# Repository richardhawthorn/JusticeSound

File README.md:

### Description

Justice Cross

### Features

- 28 LED display
- Charlieplex LED control
- ATTINY44 processor
- 3V operation @ 1Mhz or 8Mhz
- 1x button
- ICSP port
- Hole for necklace chain

### License

This work is licensed under a Creative Commons Attribution-ShareAlike 4.0 International License.

<br />
Designed by <a xmlns:cc="http://creativecommons.org/ns#" href="http://www.richardhawthorn.com" property="cc:attributionName" rel="cc:attributionURL" target="_blank">Richard Hawthorn</a><br />
<a rel="license" href="http://creativecommons.org/licenses/by-sa/4.0/" target="_blank">View License</a>

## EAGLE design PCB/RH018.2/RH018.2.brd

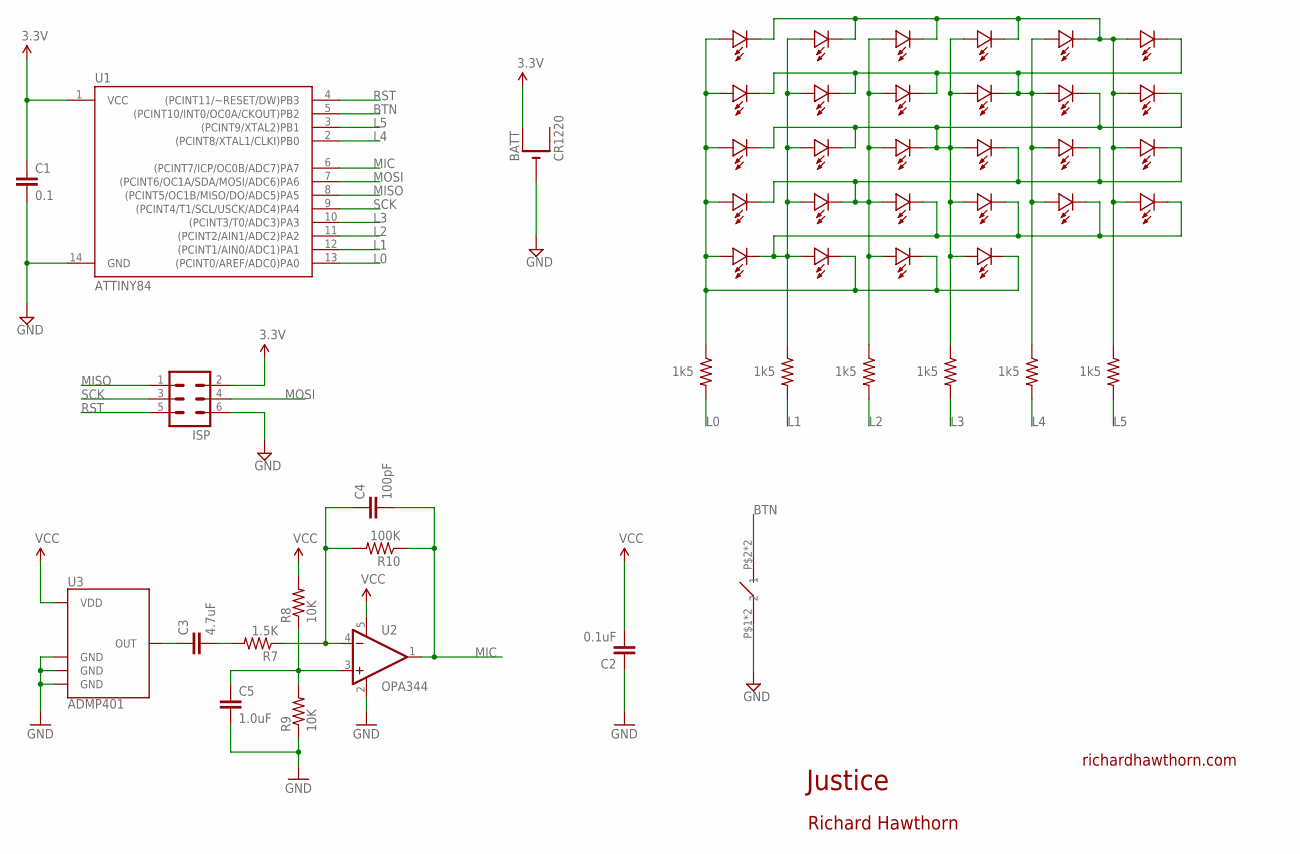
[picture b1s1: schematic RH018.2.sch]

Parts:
BATT: CR1220; CR1220-SMD
BTN1: TURTLE-3PIN
C1: 0.1; 0603-CAP
C2: 0.1uF; 0402-CAP
C3: 4.7uF; 0402-CAP
C4: 100pF; 0402-CAP
C5: 1.0uF; 0402-CAP
ISP: MA03-2
LED1, LED2, LED3, LED4, LED5, LED6, LED7, LED8, LED9, LED10, LED11, LED12, LED13, LED14, LED15, LED16, LED17, LED18, LED19, LED20, LED21, LED22, LED23, LED24, LED25, LED26, LED27, LED28: LED0603; 0603-LED
R1, R2, R3, R4, R5, R6: 1k5; 0603-RES
R7: 1.5K; 0402-RES
R8, R9: 10K; 0402-RES
R10: 100K; 0402-RES
U1: ATTINY84; SO14
U2: OPA344; SOT23-5
U3: ADMP401

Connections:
BTN: BTN1.P$2 (2), BTN1.P$4 (2), U1.5 ((PCINT10/INT0/OC0A/CKOUT)PB2)
C7N$1: C3.1, U3.1 (OUT)
GND: BATT.-, BTN1.P$1 (1), BTN1.P$3 (1), C1.2, C2.1, C5.2, ISP.6, R9.1, U1.14 (GND), U2.2 (V-), U3.2 (GND), U3.4 (GND), U3.6 (GND)
L0: R1.2, U1.13 ((PCINT0/AREF/ADC0)PA0)
L1: R2.2, U1.12 ((PCINT1/AIN0/ADC1)PA1)
L2: R3.2, U1.11 ((PCINT2/AIN1/ADC2)PA2)
L3: R4.2, U1.10 ((PCINT3/T0/ADC3)PA3)
L4: R5.2, U1.2 ((PCINT8/XTAL1/CLKI)PB0)
L5: R6.2, U1.3 ((PCINT9/XTAL2)PB1)
MIC: C4.2, R10.1, U1.6 ((PCINT7/ICP/OC0B/ADC7)PA7), U2.1 (OUT)
MISO: ISP.1, U1.8 ((PCINT5/OC1B/MISO/DO/ADC5)PA5)
MOSI: ISP.4, U1.7 ((PCINT6/OC1A/SDA/MOSI/ADC6)PA6)
unnamed: C4.1, R7.1, R10.2, U2.4 (-IN)
unnamed: C3.2, R7.2
unnamed: C5.1, R8.1, R9.2, U2.3 (+IN)
unnamed: LED1.MINUS, LED2.MINUS, LED3.MINUS, LED4.MINUS, LED5.MINUS, LED6.PLUS, LED12.PLUS, LED18.PLUS, LED24.PLUS, R6.1
unnamed: LED2.PLUS, LED8.PLUS, LED14.PLUS, LED20.PLUS, LED21.MINUS, LED22.MINUS, LED23.MINUS, LED24.MINUS, LED25.MINUS, LED26.PLUS, R2.1
unnamed: LED1.PLUS, LED7.PLUS, LED13.PLUS, LED19.PLUS, LED25.PLUS, LED26.MINUS, LED27.MINUS, LED28.MINUS, R1.1
unnamed: LED5.PLUS, LED6.MINUS, LED7.MINUS, LED8.MINUS, LED9.MINUS, LED10.MINUS, LED11.PLUS, LED17.PLUS, LED23.PLUS, R5.1
unnamed: LED4.PLUS, LED10.PLUS, LED11.MINUS, LED12.MINUS, LED13.MINUS, LED14.MINUS, LED15.MINUS, LED16.PLUS, LED22.PLUS, LED28.PLUS, R4.1
unnamed: LED3.PLUS, LED9.PLUS, LED15.PLUS, LED16.MINUS, LED17.MINUS, LED18.MINUS, LED19.MINUS, LED20.MINUS, LED21.PLUS, LED27.PLUS, R3.1
RST: ISP.5, U1.4 ((PCINT11/~RESET/DW)PB3)
SCK: ISP.3, U1.9 ((PCINT4/T1/SCL/USCK/ADC4)PA4)
VCC: BATT.+$1 (+), C1.1, C2.2, ISP.2, R8.2, U1.1 (VCC), U2.5 (V+), U3.5 (VDD)

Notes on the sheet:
Justice
richardhawthorn.com
Richard Hawthorn

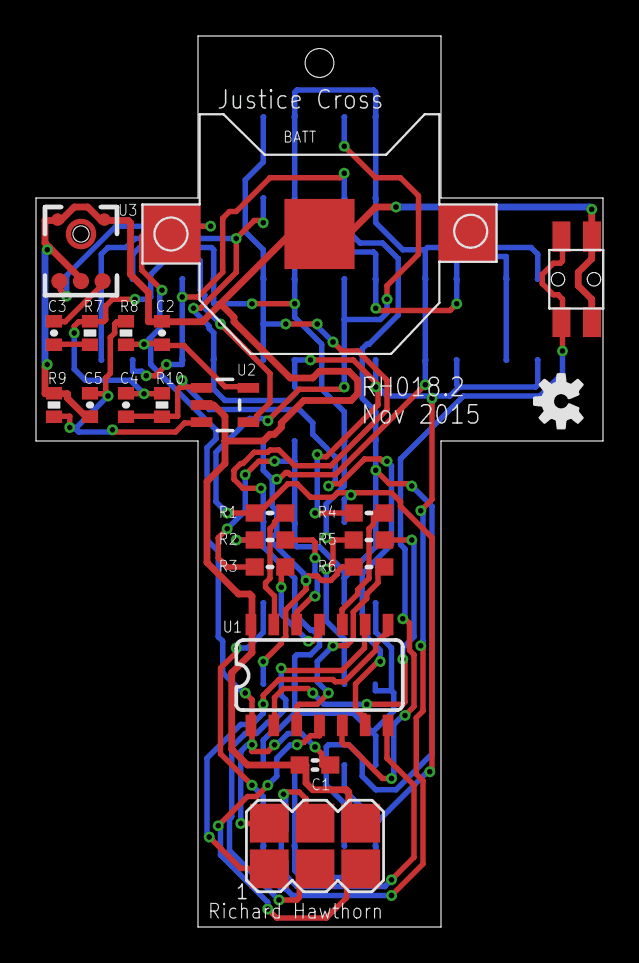
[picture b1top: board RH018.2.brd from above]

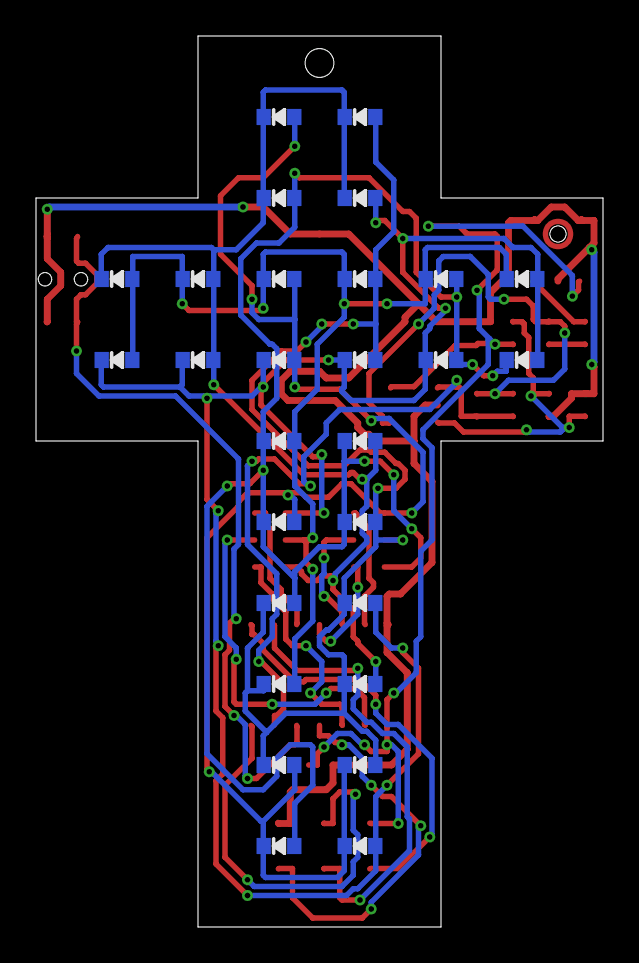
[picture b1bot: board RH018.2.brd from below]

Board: 2 copper layers, 31.5 x 49.5 mm, 50 parts (28 on the bottom side), 24 nets.

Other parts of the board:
U$3: OSHW-LOGO-S

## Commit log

2015-10-01 First version of 1.1
2015-10-01 adding v1.2
2015-11-05 Rename files
2015-11-05 update silk screen
2015-11-05 added back pcb image
2015-11-05 updated images
2015-11-05 added gerbers
2016-11-08 Adding a laser cut enclosure
2016-11-08 added readme
2016-11-10 add first version of the Arduino code

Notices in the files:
parts and their libraries:
SparkFun-Aesthetics: Licensing: CC v3.0 Share-Alike You are welcome to use this library for commercial purposes.
SparkFun-DigitalIC: Licensing: Creative Commons ShareAlike 4.0 International - https://creativecommons.org/licenses/by-sa/4.0
